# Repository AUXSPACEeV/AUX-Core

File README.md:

# `AUX-Core`

> Core/Sensor PCB of the Auxspace Avionics stack, built around an ESP32-S3-WROOM-1.

AUX-Core is our first stackable flight computer.
It operates on a powerful ESP32S3 MCU with sensors for attitude tracking,
9V USB Power Delivery or an external Power source and can interface
with other Auxspace Avionics stack components, such as
[AUX-Pwr](https://github.com/AUXSPACEeV/AUX-Pwr) or
[AUX-Tel](https://github.com/AUXSPACEeV/AUX-Tel).

## Features

* **Barometer** DPS310/DPS368 for altitude computation
* **IMU** STM LSM6DSO32x for acceleration and rotation data
* **High-G accelerometer** STM LSM6DSV320XTR (±320 g) when things get tough
* **Magnetometer** STM LIS3MDL for attitude reference
* **Buzzer** for easier commissioning and recovery
* **CAN bus** (TCAN334) for communication with the other stack PCBs
* **µSD card** for logging
* **USB-C with 9 V Power Delivery** (CH224A sink) for programming, debugging and supply
* **Stack connector** Samtec TFM-110-02-S-D-A / SFM-110-02-L-D-A for the avionics stack
* **Status LEDs** for power, SD activity and board state

## Stack connector

The board carries a mating Samtec pin/socket pair (2x10, 1.27 mm), so Core boards and
expansion PCBs stack directly on top of each other. The connector routes the switched and
unswitched VBus rails, CAN, I²C, UART and the ARM signal through the stack.

## Power supply

The board is supplied over USB-C. The CH224A PD sink negotiates 9 V from the charger; the
on-board TPS7B8601 regulator derives the 3V3 rail from it. VBus is distributed to the stack
both directly and through the switched rails.

## Programming

The ESP32-S3 is programmed via USB-C or the UART connection.
To enter download mode, press and hold BOOTSEL at startup.

## Repository layout

| Folder                                                     | Content                                          |
| ---------------------------------------------------------- | ------------------------------------------------ |
| [`1_Blockschaltbild`](./1_Blockschaltbild)                 | Block diagrams                                    |
| [`2_Designunterlagen`](./2_Designunterlagen)               | Pin maps, calculations and design documents       |
| [`3_Elektronik`](./3_Elektronik)                           | KiCad project, symbols, footprints and 3D models  |
| [`4_Simulationen`](./4_Simulationen)                       | LTspice simulations                               |
| [`5_Tests`](./5_Tests)                                     | Test results and oscillograms                     |
| [`6_Export-Fertigungsdaten`](./6_Export-Fertigungsdaten)   | Manufacturing data, BOMs, schematics and STEP files |

## License

Hardware is released under the CERN Open Hardware Licence Version 2 - Permissive,
see [`LICENSE`](./LICENSE).

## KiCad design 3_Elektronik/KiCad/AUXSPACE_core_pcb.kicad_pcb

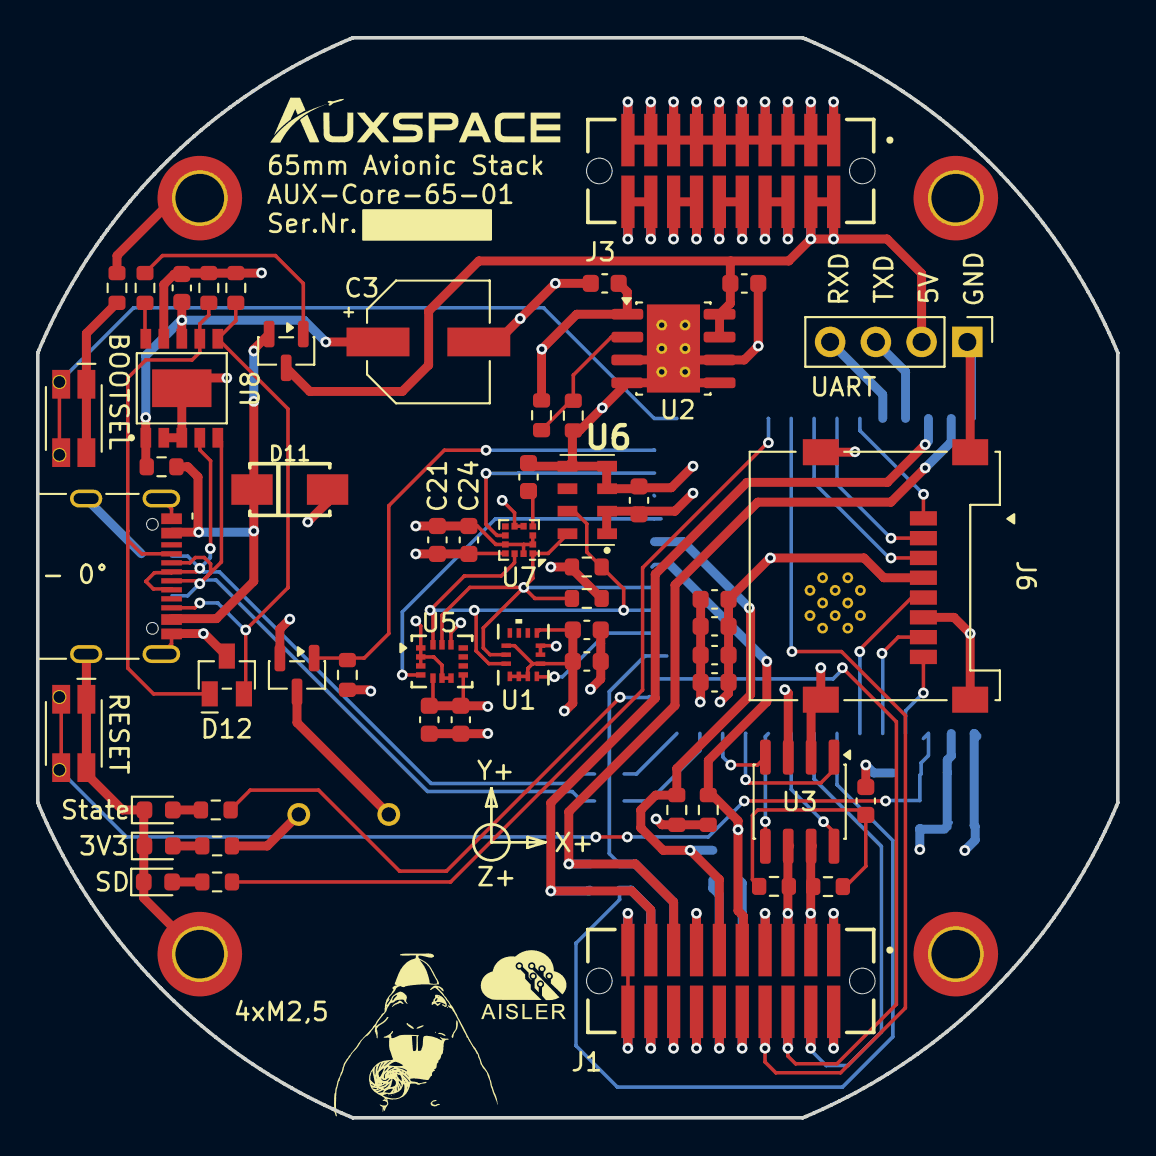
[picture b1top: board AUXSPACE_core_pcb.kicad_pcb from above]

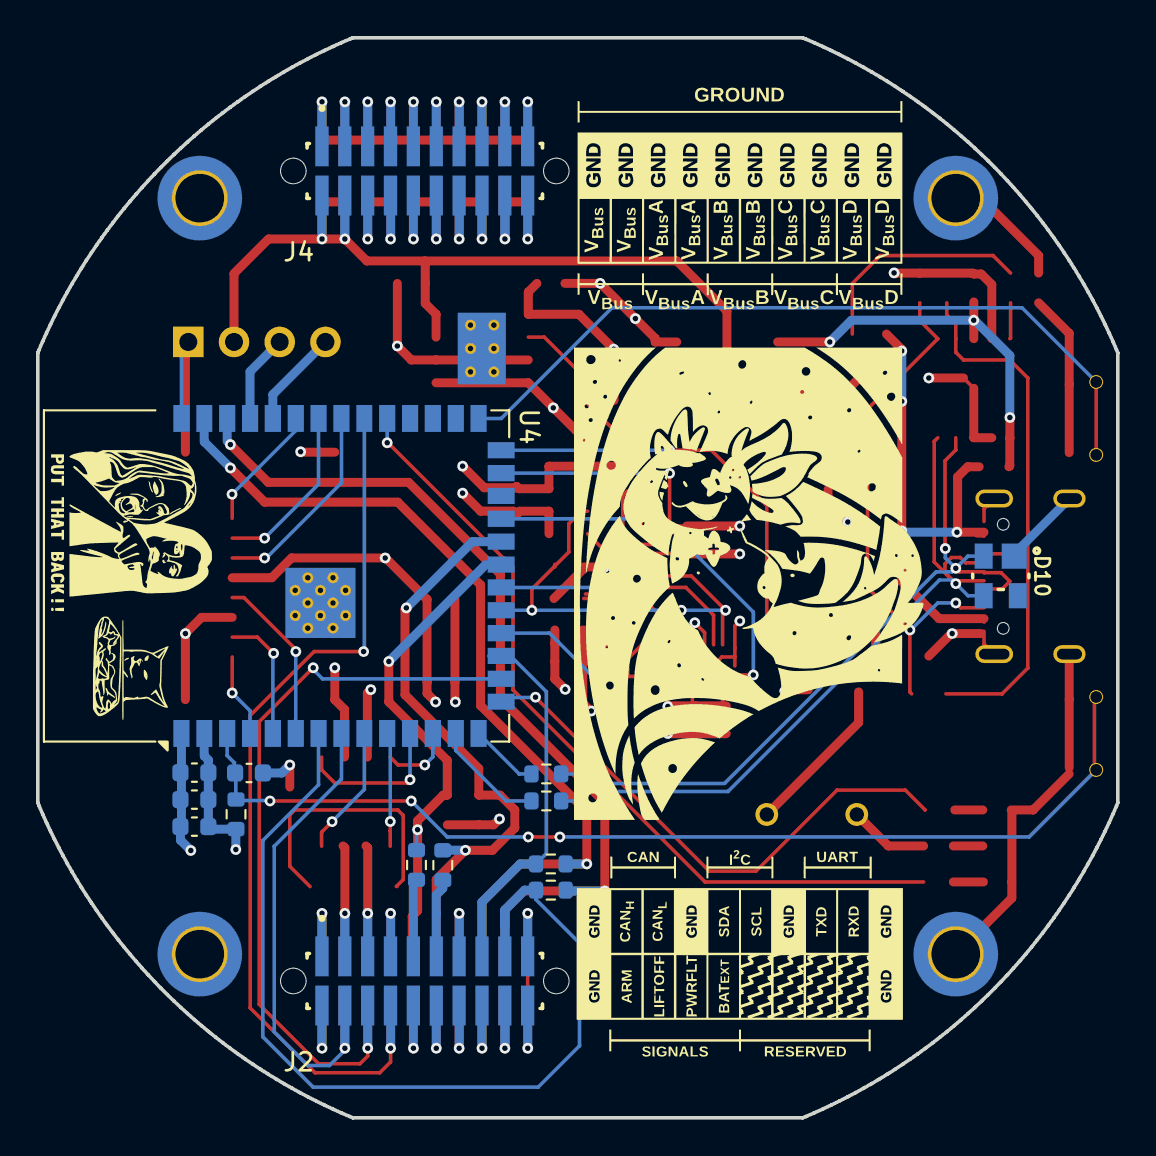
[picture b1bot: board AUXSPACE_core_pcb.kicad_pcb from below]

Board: 4 copper layers, 60.0 x 60.0 mm, 78 parts (15 on the bottom side), 65 nets.

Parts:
BZ1: WST-0904T; Buzzer_WST-0906T
C3: 150 µF; CP_Wurth_WCAP-ASLL-D6.3L5.5
C4, C5, C8, C9, C12, C13, C14, C16, C18, C20, C22, C23, C24: 100nF; C_0603_1608Metric
C7, C15, C25: 10µF; C_0603_1608Metric
C10, C17, C19, C21: 1µF; C_0603_1608Metric
D3, D4, D5: green; LED_0603_1608Metric
D10: 8240136; WE-TVS_SOT143-4L
D11: SMAJ22A; WE-TVS_SMAJ22A
D12: 824094024; WE-TVS_824094024_SOT23-3L
H1, H2, H3, H4: MountingHole_Pad; MountingHole_2.7mm_M2.5_DIN965_Pad_TopBottom
J1, J3: Conn_02x10_Odd_Even; SAMTEC_TFM-110-02-S-D-A
J2, J4: Conn_02x10_Odd_Even; SAMTEC_SFM-110-02-L-D-A-P-TR
J5: Conn_01x04_Pin; PinHeader_1x04_P2.54mm_Vertical
J6: 693072010801; J_Wurth_WR-CRD_693072010801
J7: 629722000214; J_Wurth_WR-USB_629722000214
Logo1: aisler_logo_5mm
Logo2, Logo2#2: AUXSPACE_Logo_2_5mm
Q1: 2N7002K; SOT-23
Q2: DMP3099L; SOT-23
R1, R3, R5, R7: 0R; R_0603_1608Metric
R2, R17: 62R; R_0603_1608Metric
R4, R15: 11k; R_0603_1608Metric
R6, R18, R21, R22: 2,7k; R_0603_1608Metric
R9, R10, R11, R14, R16, R23: 4,7k; R_0603_1608Metric
R19, R20: 22R; R_0603_1608Metric
R30, R33: 5,1k; R_0603_1608Metric
R32: 100k; R_0603_1608Metric
R34: 10k; R_0603_1608Metric
SW2, SW3: 434331013822; SW_Wurth_WS-TASU_434331013822
U1: LSM6DSV320XTR; LGA-14L_2p5X3X0p83_STM
U2: TPS7B8601QDDARQ1; Texas_R-PDSO-G8_EP2.95x4.9mm_Mask2.4x3.1mm_ThermalVias
U3: TCAN334; SOIC-8_3.9x4.9mm_P1.27mm
U4: ESP32-S3-WROOM-1
U5: LSM6DSO32XTR; LGA_O32XTR_STM
U6: MS5607-02BA; MS5607-02BA03
U7: LIS3MDL; LGA-12_2x2mm_P0.5mm
U8: CH224A; ESSOP-10-1EP_3.9x5.0mm_P1mm_EP2.1x3.3mm

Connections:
+3V3: BZ1.1 (+), C5.1, C7.2, C8.2, C9.1, C10.1, C12.1, C14.1, C15.1, C17.1, C18.1, C21.1, C22.2, C23.2, C24.1, C25.1, J6.4 (VDD), R4.1, R9.2, R10.2, R14.2, R15.1, R16.2, R18.2, U1.1 (SDO/TA0), U1.2 (SDX), U1.3 (SCX), U1.5 (VDDIO), U1.8 (VDD), U1.12 (CS), U2.1 (OUT), U3.3 (VCC), U4.2 (3V3), U5.5 (Vdd_IO), U5.8 (Vdd), U5.12 (CS), U6.1 (VDD), U6.2 (PS), U7.5 (Vdd), U7.6 (Vdd_IO), U7.10 (~CS)
/Baseboard/ARM: J1.4, J2.4, U4.8 (IO15)
/Baseboard/Bat on ext: J1.10, J2.10
/Baseboard/CAN_H: J1.3, J2.3, R2.1, U3.7 (CANH)
/Baseboard/CAN_L: J1.5, J2.5, R17.2, U3.6 (CANL)
/Baseboard/I2C_SCL_bot: J2.11, R5.1
/Baseboard/I2C_SCL_top: J1.11, R5.2, R14.1, U4.22 (IO14)
/Baseboard/I2C_SDA_bot: J2.9, R7.1
/Baseboard/I2C_SDA_top: J1.9, R7.2, R16.1, U4.21 (IO13)
/Baseboard/LIFTOFF: J1.6, J2.6, U4.16 (IO46)
/Baseboard/Power Fault: J1.8, J2.8, U4.32 (IO39)
/Baseboard/UART_RX_bot: J2.17, R1.1, U4.7 (IO7)
/Baseboard/UART_RX_top: J1.17, R1.2, U4.38 (IO2)
/Baseboard/UART_TX_bot: J2.15, R3.1, U4.17 (IO9)
/Baseboard/UART_TX_top: J1.15, R3.2, U4.39 (IO1)
/Baseboard/VBus_switched_A: J3.6, J3.8, J4.6, J4.8
/Baseboard/VBus_switched_B: J3.10, J3.12, J4.10, J4.12
/Baseboard/VBus_switched_C: J3.14, J3.16, J4.14, J4.16
/Baseboard/VBus_switched_D: J3.18, J3.20, J4.18, J4.20
/Baseboard/reserved_1: J1.12, J2.12
/Baseboard/reserved_2: J1.14, J2.14
/Baseboard/reserved_3: J1.16, J2.16
/Baseboard/reserved_4: J1.18, J2.18
/MCU/ACCEL_INT1: U1.4 (INT1), U4.18 (IO10)
/MCU/Buzzer: Q1.1 (G), R11.1, U4.26 (IO45)
/MCU/CAN_RXD: U3.4 (RXD), U4.12 (IO8)
/MCU/CAN_SHDN: U3.5 (SHDN), U4.10 (IO17)
/MCU/CAN_STB: U3.8 (STB), U4.9 (IO16)
/MCU/CAN_TXD: U3.1 (TXD), U4.11 (IO18)
/MCU/I2C0_SCL: R9.1, U1.13 (SCL), U4.20 (IO12), U5.13 (SCL), U6.8 (SCLK), U7.1 (SCL/SPC)
/MCU/I2C0_SDA: R10.1, U1.14 (SDA), U4.19 (IO11), U5.14 (SDA), U6.7 (SDI/SDA), U7.11 (SDA/SDI/SDO)
/MCU/IMU_INT: U4.23 (IO21), U5.4 (INT1)
/MCU/IO0: SW3.3, SW3.4, SW3.5, SW3.6, U4.27 (IO0)
/MCU/MAG_DRDY: U4.25 (IO48), U7.8 (DRDY)
/MCU/MCU_EN: C13.1, R15.2, SW2.3, SW2.4, SW2.5, SW2.6, U4.3 (EN)
/MCU/RX: J5.4, U4.36 (RXD0)
/MCU/SD_CD/DAT3_CS: J6.2 (CD/DAT3), U4.34 (IO41)
/MCU/SD_CLK: J6.5 (CLK), U4.6 (IO6)
/MCU/SD_CMD_MOSI: J6.3 (CMD), U4.33 (IO40)
/MCU/SD_DAT0_MISO: J6.7 (DAT0), U4.5 (IO5)
/MCU/SD_DAT1: J6.8 (DAT1), U4.4 (IO4)
/MCU/SD_DAT2: J6.1 (DAT2), U4.35 (IO42)
/MCU/SD_LED: R22.2, U4.31 (IO38)
/MCU/STATE_LED: R21.2, U4.15 (IO3)
/MCU/TX: J5.3, U4.37 (TXD0)
/Power/CC1: D12.1 (I/O1), J7.A5 (CC1), R33.1, U8.7 (CC1)
/Power/CC2: D12.2 (I/O2), J7.B5 (CC2), R30.1, U8.6 (CC2)
/Power/USB_D+: D10.2, J7.A6 (D+1), J7.B6 (D+2), R20.1, U8.4 (DP)
/Power/USB_D-: D10.3, J7.A7 (D-1), J7.B7 (D-2), R19.1, U8.5 (DM)
GND: C3.2, C4.2, C5.2, C7.1, C8.1, C9.2, C10.2, C12.2, C13.2, C14.2, C15.2, C16.1, C17.2, C18.2, C19.1, C20.1, C21.2, C22.1, C23.1, C24.2, C25.2, D3.1 (K), D4.1 (K), D5.1 (K), D10.1, D11.2, D12.3 (GND), H1.1 (1_1), H2.1 (1_1), H3.1 (1_1), H4.1 (1_1), J1.1, J1.2, J1.7, J1.13, J1.19, J1.20, J2.1, J2.2, J2.7, J2.13, J2.19, J2.20, J3.1, J3.3, J3.5, J3.7, J3.9, J3.11, J3.13, J3.15, J3.17, J3.19, J4.1, J4.3, J4.5, J4.7, J4.9, J4.11, J4.13, J4.15, J4.17, J4.19, J5.1, J6.6 (VSS), J6.S1 (SHIELD), J6.S2 (SHIELD), J6.S3 (SHIELD), J6.S4 (SHIELD), J7.A1 (GND), J7.A12 (GND1), J7.B1 (GND3), J7.B12 (GND2), J7.S1 (SHIELD), J7.S2 (SHIELD), J7.S3 (SHIELD), J7.S4 (SHIELD), Q1.2 (S), R6.2, R11.2, R23.1, R30.2, R33.2, SW2.1, SW2.2, U1.6 (GND), U1.7 (GND), U2.3 (NC), U2.4 (NC), U2.5 (GND), U2.6 (NC), U2.9 (Thermal_Pad), U3.2 (GND), U4.1 (GND), U4.40 (GND), U4.41 (GND), U5.1 (SDO/SA0), U5.2 (SDx), U5.3 (SCx), U5.6 (GND), U5.7 (GND), U6.3 (GND), U6.4 (CSB), U6.5 (CSB), U7.2 (GND), U7.3 (GND), U7.9 (SDO/SA1), U7.12 (GND), U8.2 (CFG2/SCL), U8.3 (CFG3/SDA), U8.9 (CFG1), U8.11 (GND)
unnamed: BZ1.2 (-), Q1.3 (D)
unnamed: C16.2, R2.2, R17.1
unnamed: D3.2 (A), R18.1
unnamed: D4.2 (A), R21.1
unnamed: D5.2 (A), R22.1
unnamed: Q2.1 (G), R34.1
unnamed: R23.2, SW3.1, SW3.2
unnamed: R4.2, R6.1, U2.2 (FB)
unnamed: R20.2, U4.14 (USB_D+)
unnamed: R19.2, U4.13 (USB_D-)
unnamed: C20.2, U7.4 (C1)
unnamed: R34.2, U8.10 (PG)
unnamed: C3.1, C19.2, R32.2, U8.1 (VHV), U8.8 (VBUS)
VBus_direct: C4.1, J3.2, J3.4, J4.2, J4.4, J5.2, Q2.3 (D), U2.7 (EN), U2.8 (IN)
Vusb: D11.1, J7.A4 (VBUS), J7.A9 (VBUS1), J7.B4 (VBUS3), J7.B9 (VBUS2), Q2.2 (S), R32.1
